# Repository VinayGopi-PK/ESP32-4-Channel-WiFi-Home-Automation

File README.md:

# ESP32 4-Channel Wi-Fi Home Automation

An **ESP32-based 4-channel Wi-Fi Home Automation Controller** designed for wireless control of electrical loads using four relay outputs.

The project includes a custom hardware design developed in **KiCad**, covering the schematic, PCB layout, power supply section, ESP32 programming interface, relay control circuitry, indicators, and PCB 3D visualization.

---

## Project Overview

This project is a compact **4-channel Wi-Fi Home Automation Controller** based on an ESP32 module.

The controller is designed to provide four independent relay-controlled outputs that can be operated through the ESP32's Wi-Fi connectivity.

The PCB integrates the ESP32 controller, isolated AC-to-DC power supply, 3.3 V regulation, USB programming interface, relay control circuitry, status indicators, and four relay outputs into a single custom PCB.

### Basic System Architecture

```text
                    AC INPUT
                       │
                       ▼
              ┌─────────────────┐
              │  Isolated AC-DC │
              │   Power Supply  │
              └────────┬────────┘
                       │
                       ▼
                  +5V DC Rail
                       │
             ┌─────────┴─────────┐
             │                   │
             ▼                   ▼
       3.3V Regulator       Relay Section
             │                   │
             ▼                   ▼
          ESP32 MCU        4 × Relays
             │                   │
             └─────────┬─────────┘
                       │
                 Wi-Fi Control
                       │
                       ▼
                 Home Appliances
```

---

## Main Features

* ESP32-based Wi-Fi controller
* 4 independent relay channels
* Custom PCB designed using KiCad
* Isolated AC-to-DC power supply section
* 5 V system power rail
* 3.3 V regulated supply for ESP32
* USB interface for programming and communication
* CP2102 USB-to-UART interface
* Auto-programming support
* BOOT and RESET controls
* Individual relay control circuitry
* Status indication LEDs
* Custom PCB layout
* Front and back copper routing
* 3D PCB visualization
* Manufacturing-oriented PCB design

---

## Hardware

| Component         | Function                                    |
| ----------------- | ------------------------------------------- |
| ESP32             | Main microcontroller and Wi-Fi connectivity |
| HLK-PM01          | Isolated AC-to-DC power supply              |
| AMS1117-3.3       | 3.3 V voltage regulation                    |
| CP2102            | USB-to-UART programming interface           |
| SANYOU SRD Relays | Switching of four output channels           |
| SS14              | Power protection / rectification section    |
| BOOT Button       | ESP32 boot-mode control                     |
| RESET Button      | ESP32 reset control                         |
| Status LEDs       | Power / system / channel indication         |
| Micro USB         | Power/programming interface                 |

---

## 4-Channel Relay Control

The PCB provides **four independent relay channels** for controlling external electrical loads.

```text
                    ESP32
                      │
          ┌───────────┼───────────┐───────────┐   
          │           │           │           │
          ▼           ▼           ▼           ▼
       Channel 1   Channel 2   Channel 3   Channel 4
          │           │           │           │
          ▼           ▼           ▼           ▼
       Relay 1     Relay 2     Relay 3     Relay 4
          │           │           │           │
          ▼           ▼           ▼           ▼
       LOAD 1      LOAD 2      LOAD 3      LOAD 4
```

Each relay channel is controlled independently by the ESP32.

---

## Power Supply

The PCB incorporates an **isolated AC-to-DC power supply section** to provide the required DC power for the controller.

The power architecture includes:

* AC input
* Isolated AC-to-DC conversion
* +5 V system rail
* 3.3 V regulation
* ESP32 power supply
* Relay power supply
* Power protection components

The design separates the low-voltage control circuitry from the incoming AC section through the isolated power supply.

---

## USB Programming Interface

The PCB includes a **CP2102 USB-to-UART interface** for programming and serial communication with the ESP32.

The programming section includes:

* Micro USB connector
* CP2102 USB-to-UART bridge
* ESP32 UART connection
* Auto-programming circuitry
* BOOT control
* RESET control

This allows the ESP32 firmware to be programmed without requiring a separate external USB-to-UART module.

---

## Indicators and Controls

The design includes dedicated user-interface components for operating and monitoring the controller.

### Controls

* BOOT button
* RESET button

### Indicators

* Power/system status indication
* Relay/channel status indication

The PCB uses compact SMD LEDs for status indication while retaining convenient physical controls for programming and reset operations.

---

## PCB Design

The complete PCB was designed using **KiCad**.

The design includes:

* Complete electrical schematic
* Component selection and footprint assignment
* PCB component placement
* Signal routing
* Power routing
* Ground plane
* Relay section
* AC input section
* USB programming section
* ESP32 section
* Front and back PCB layout
* 3D PCB visualization
* Manufacturing files

---

## PCB Design Preview

### Schematic

### PCB Front Layout

### PCB Back Layout

### 3D View

---

## Design Considerations

The PCB design considers the separation between the **AC mains section and low-voltage electronics**.

Important design considerations include:

* Isolation between AC input and low-voltage circuitry
* Dedicated power distribution
* Ground-plane implementation
* Appropriate PCB clearances
* Relay switching section
* ESP32 signal routing
* USB programming interface
* Component placement
* Manufacturing requirements

> **Safety note:** This project involves mains-voltage circuitry. The PCB should only be assembled, tested, and operated by appropriately qualified personnel using suitable electrical safety practices and enclosure/isolation measures.

---

## Design Tools

* **KiCad** — Schematic and PCB design
* **ESP32** — Embedded Wi-Fi controller
* **CP2102** — USB-to-UART interface

---

## Technical Highlights

**Microcontroller:** ESP32
**Wireless Communication:** Wi-Fi
**Relay Channels:** 4
**AC-DC Power Supply:** HLK-PM01
**Logic Supply:** 3.3 V
**USB-UART:** CP2102
**Relay:** SANYOU SRD Series
**PCB Design Tool:** KiCad
**PCB Type:** Custom PCB

---

## Repository Contents

The repository contains the project design files, PCB manufacturing files, documentation, and project images.

### KiCad Project

Contains:

* KiCad schematic
* KiCad PCB layout
* KiCad project files
* Component and footprint configuration files

### Documentation

Contains project-related documentation and component information.

### Gerber Files

Contains the generated PCB manufacturing files.

### Images

Contains:

* Schematic
* PCB front layout
* PCB back layout
* PCB 3D view

---

## Project Objective

The objective of this project was to design a **compact 4-channel ESP32-based Wi-Fi Home Automation Controller** integrating wireless control, relay switching, isolated power conversion, USB programming, and custom PCB design into a single hardware platform.

The project demonstrates skills in:

* Embedded system hardware design
* ESP32-based systems
* Wi-Fi-enabled control systems
* Power supply design
* Relay control
* USB-to-UART programming
* Schematic design
* PCB layout
* Component selection
* PCB manufacturing file generation

---

## Project Type

**ESP32 Embedded System | Wi-Fi Home Automation | Relay Controller | PCB Design**

**Design Software:** KiCad
**Controller:** ESP32

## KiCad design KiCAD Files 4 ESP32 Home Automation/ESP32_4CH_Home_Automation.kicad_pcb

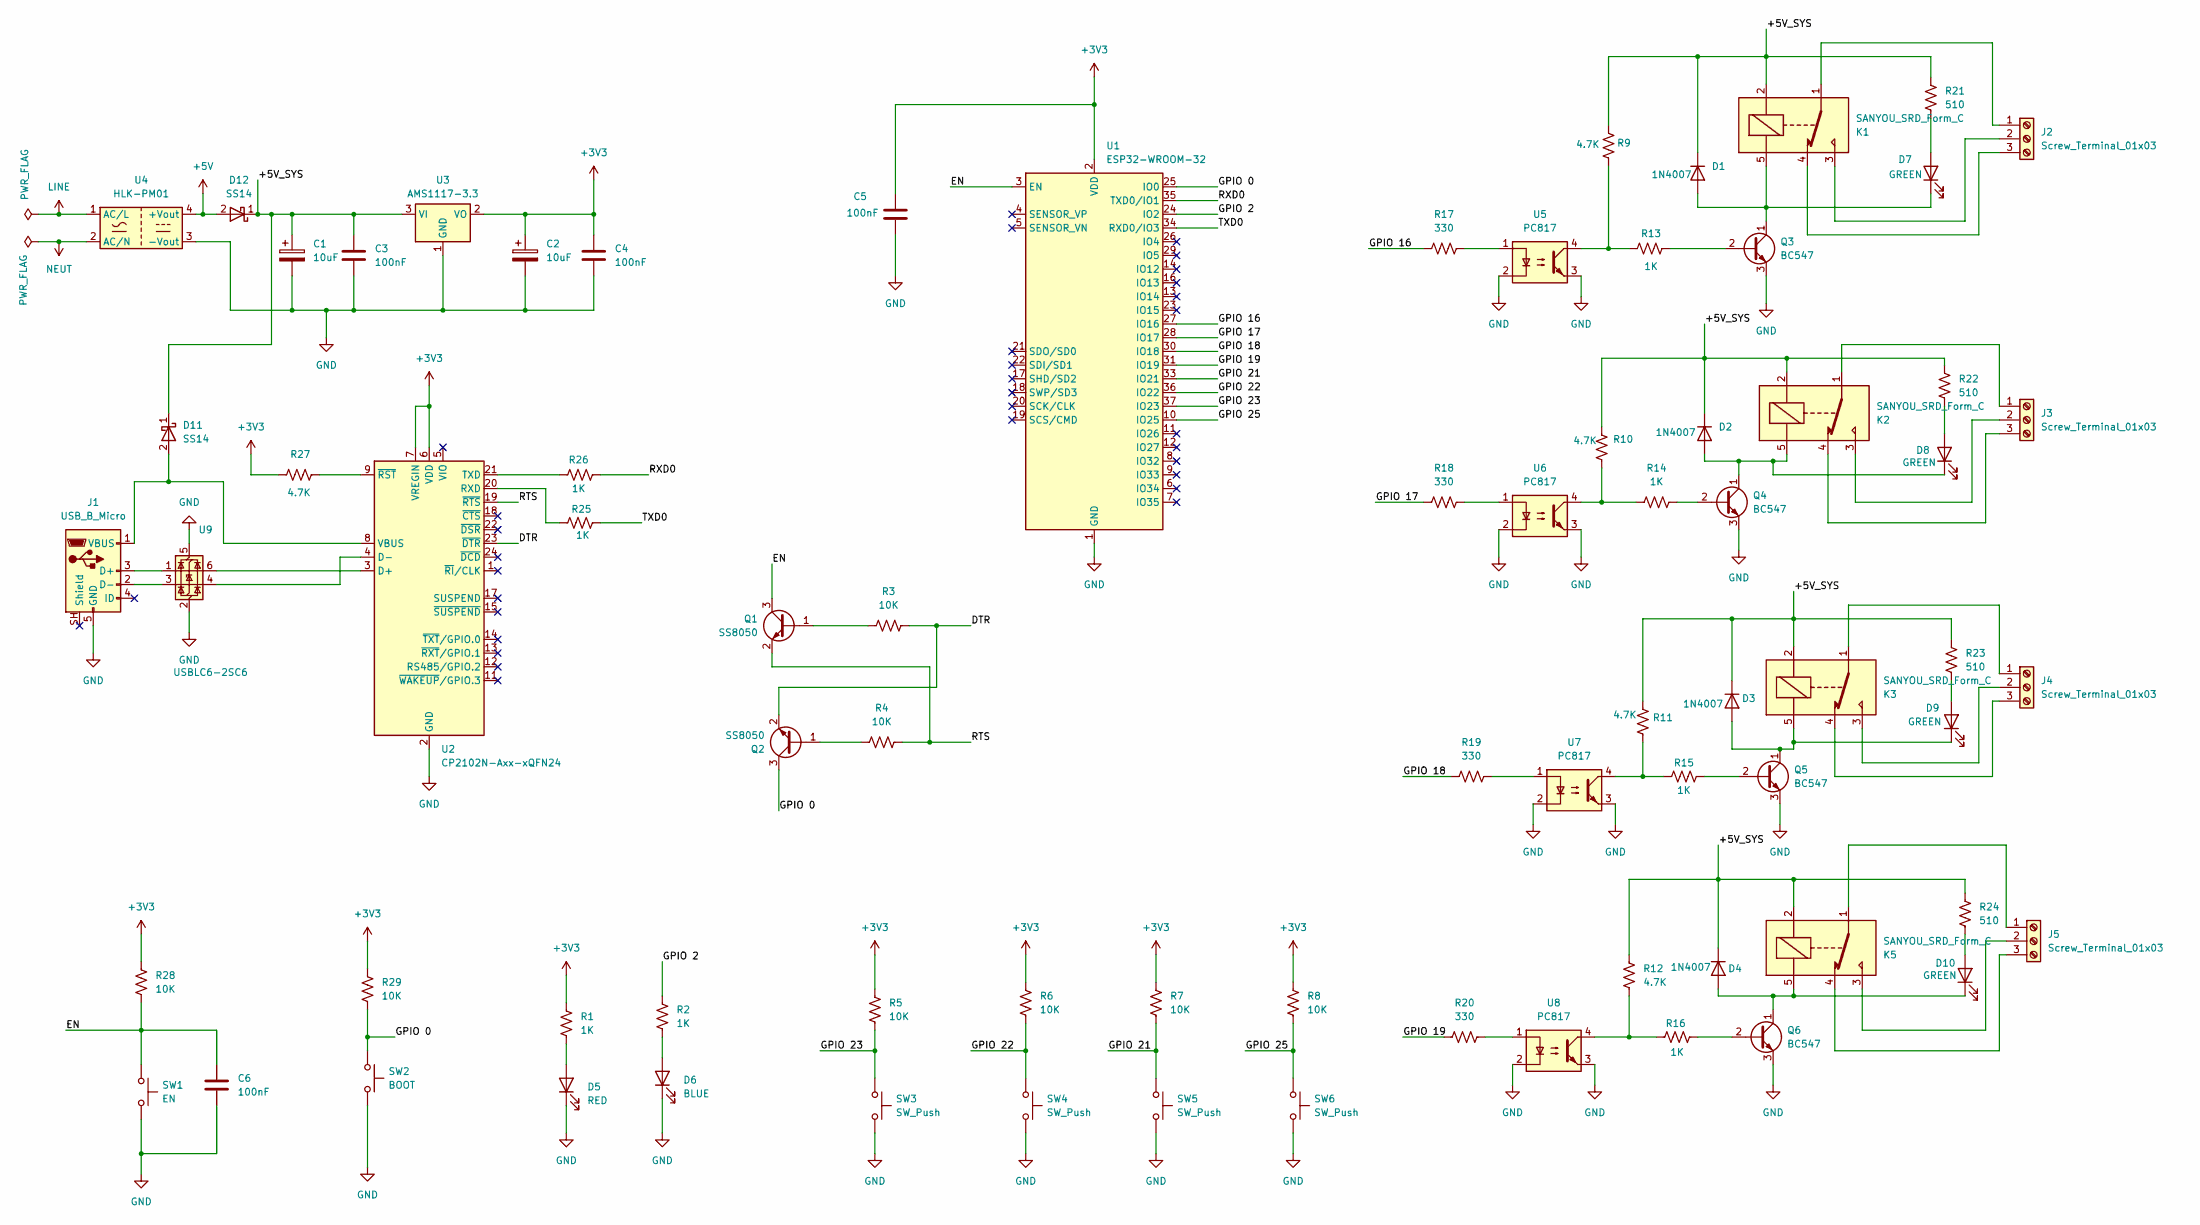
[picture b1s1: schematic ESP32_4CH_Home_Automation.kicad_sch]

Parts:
C1, C2: 10uF; C_1206_3216Metric
C3, C4, C5, C6: 100nF; C_0805_2012Metric
D1, D2, D3, D4: 1N4007; D_DO-41_SOD81_P10.16mm_Horizontal
D5: RED; LED_1206_3216Metric
D6: BLUE; LED_1206_3216Metric
D7, D8, D9, D10: GREEN; LED_1206_3216Metric
D11, D12: SS14; D_SMA
J1: USB_B_Micro; USB_Micro-B_Molex-105017-0001
J2, J3, J4, J5: Screw_Terminal_01x03; TerminalBlock_Phoenix_MKDS-1,5-3-5.08_1x03_P5.08mm_Horizont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
K1, K2, K3, K5: SANYOU_SRD_Form_C; Relay_SPDT_SANYOU_SRD_Series_Form_C
Q1, Q2: SS8050; SOT-23
Q3, Q4, Q5, Q6: BC547; TO-92_Inline
R1, R2, R25, R26: 1K; R_0805_2012Metric
R3, R4, R5, R6, R7, R8, R28, R29: 10K; R_0805_2012Metric
R9, R10, R11, R12: 4.7K; R_Axial_DIN0207_L6.3mm_D2.5mm_P7.62mm_Horizontal
R13, R14, R15, R16: 1K; R_Axial_DIN0207_L6.3mm_D2.5mm_P7.62mm_Horizontal
R17, R18, R19, R20: 330; R_Axial_DIN0207_L6.3mm_D2.5mm_P7.62mm_Horizontal
R21, R22, R23, R24: 510; R_Axial_DIN0207_L6.3mm_D2.5mm_P7.62mm_Horizontal
R27: 4.7K; R_0805_2012Metric
SW1: EN; SW_SPST_TL3342
SW2: BOOT; SW_SPST_TL3342
SW3, SW4, SW5, SW6: SW_Push; SW_PUSH_6mm
U1: ESP32-WROOM-32
U2: CP2102N-Axx-xQFN24; QFN-24-1EP_4x4mm_P0.5mm_EP2.6x2.6mm
U3: AMS1117-3.3; SOT-223-3_TabPin2
U4: HLK-PM01; Converter_ACDC_Hi-Link_HLK-PMxx
U5, U6, U7, U8: PC817; DIP-4_W7.62mm
U9: USBLC6-2SC6; SOT-23-6

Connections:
+3V3: C2.1, C4.1, C5.1, R1.1, R5.1, R6.1, R7.1, R8.1, R27.1, R28.2, R29.1, U1.2 (VDD), U2.6 (VDD), U2.7 (VREGIN), U3.2 (VO)
+5V: D12.2 (A), U4.4 (+Vout)
/+5V_SYS: C1.1, C3.1, D1.1 (K), D2.1 (K), D3.1 (K), D4.1 (K), D11.1 (K), D12.1 (K), K1.2, K2.2, K3.2, K5.2, R9.1, R10.1, R11.1, R12.1, R21.1, R22.1, R23.1, R24.1, U3.3 (VI)
/DTR: Q2.2 (E), R3.2, U2.23 (~DTR)
/EN: C6.1, Q1.3 (C), R28.1, SW1.1, U1.3 (EN)
/GPIO 0: Q2.3 (C), R29.2, SW2.1, U1.25 (IO0)
/GPIO 2: R2.1, U1.24 (IO2)
/GPIO 16: R17.1, U1.27 (IO16)
/GPIO 17: R18.1, U1.28 (IO17)
/GPIO 18: R19.1, U1.30 (IO18)
/GPIO 19: R20.1, U1.31 (IO19)
/GPIO 21: R7.2, SW5.1, U1.33 (IO21)
/GPIO 22: R6.2, SW4.1, U1.36 (IO22)
/GPIO 23: R5.2, SW3.1, U1.37 (IO23)
/GPIO 25: R8.2, SW6.1, U1.10 (IO25)
/RTS: Q1.2 (E), R4.2, U2.19 (~RTS)
/RXD0: R26.2, U1.35 (TXD0/IO1)
/TXD0: R25.2, U1.34 (RXD0/IO3)
GND: C1.2, C2.2, C3.2, C4.2, C5.2, C6.2, D5.1 (K), D6.1 (K), J1.5 (GND), Q3.3 (E), Q4.3 (E), Q5.3 (E), Q6.3 (E), SW1.2, SW2.2, SW3.2, SW4.2, SW5.2, SW6.2, U1.1 (GND), U1.15 (GND), U1.38 (GND), U1.39 (GND), U2.2 (GND), U2.25 (GND), U3.1 (GND), U4.3 (-Vout), U5.2, U5.3, U6.2, U6.3, U7.2, U7.3, U8.2, U8.3, U9.2 (GND), U9.5 (VBUS)
LINE: U4.1 (AC/L)
NEUT: U4.2 (AC/N)
unnamed: D1.2 (A), D7.1 (K), K1.5, Q3.1 (C)
unnamed: D2.2 (A), D8.1 (K), K2.5, Q4.1 (C)
unnamed: D3.2 (A), D9.1 (K), K3.5, Q5.1 (C)
unnamed: D5.2 (A), R1.2
unnamed: D6.2 (A), R2.2
unnamed: D7.2 (A), R21.2
unnamed: D8.2 (A), R22.2
unnamed: D9.2 (A), R23.2
unnamed: D10.2 (A), R24.2
unnamed: D4.2 (A), D10.1 (K), K5.5, Q6.1 (C)
unnamed: D11.2 (A), J1.1 (VBUS), U2.8 (VBUS)
unnamed: J1.3 (D+), U9.1 (I/O1)
unnamed: J1.2 (D-), U9.3 (I/O2)
unnamed: J2.1, K1.1
unnamed: J2.2, K1.3
unnamed: J2.3, K1.4
unnamed: J3.1, K2.1
unnamed: J3.2, K2.3
unnamed: J3.3, K2.4
unnamed: J4.1, K3.1
unnamed: J4.2, K3.3
unnamed: J4.3, K3.4
unnamed: J5.1, K5.1
unnamed: J5.2, K5.3
unnamed: J5.3, K5.4
unnamed: Q1.1 (B), R3.1
unnamed: Q2.1 (B), R4.1
unnamed: Q3.2 (B), R13.2
unnamed: Q4.2 (B), R14.2
unnamed: Q5.2 (B), R15.2
unnamed: Q6.2 (B), R16.2
unnamed: R10.2, R14.1, U6.4
unnamed: R11.2, R15.1, U7.4
unnamed: R12.2, R16.1, U8.4
unnamed: R9.2, R13.1, U5.4
unnamed: R17.2, U5.1
unnamed: R18.2, U6.1
unnamed: R19.2, U7.1
unnamed: R20.2, U8.1
unnamed: U2.3 (D+), U9.6 (I/O1)
unnamed: U2.4 (D-), U9.4 (I/O2)
unnamed: R25.1, U2.20 (RXD)
unnamed: R26.1, U2.21 (TXD)
unnamed: R27.2, U2.9 (~RST)

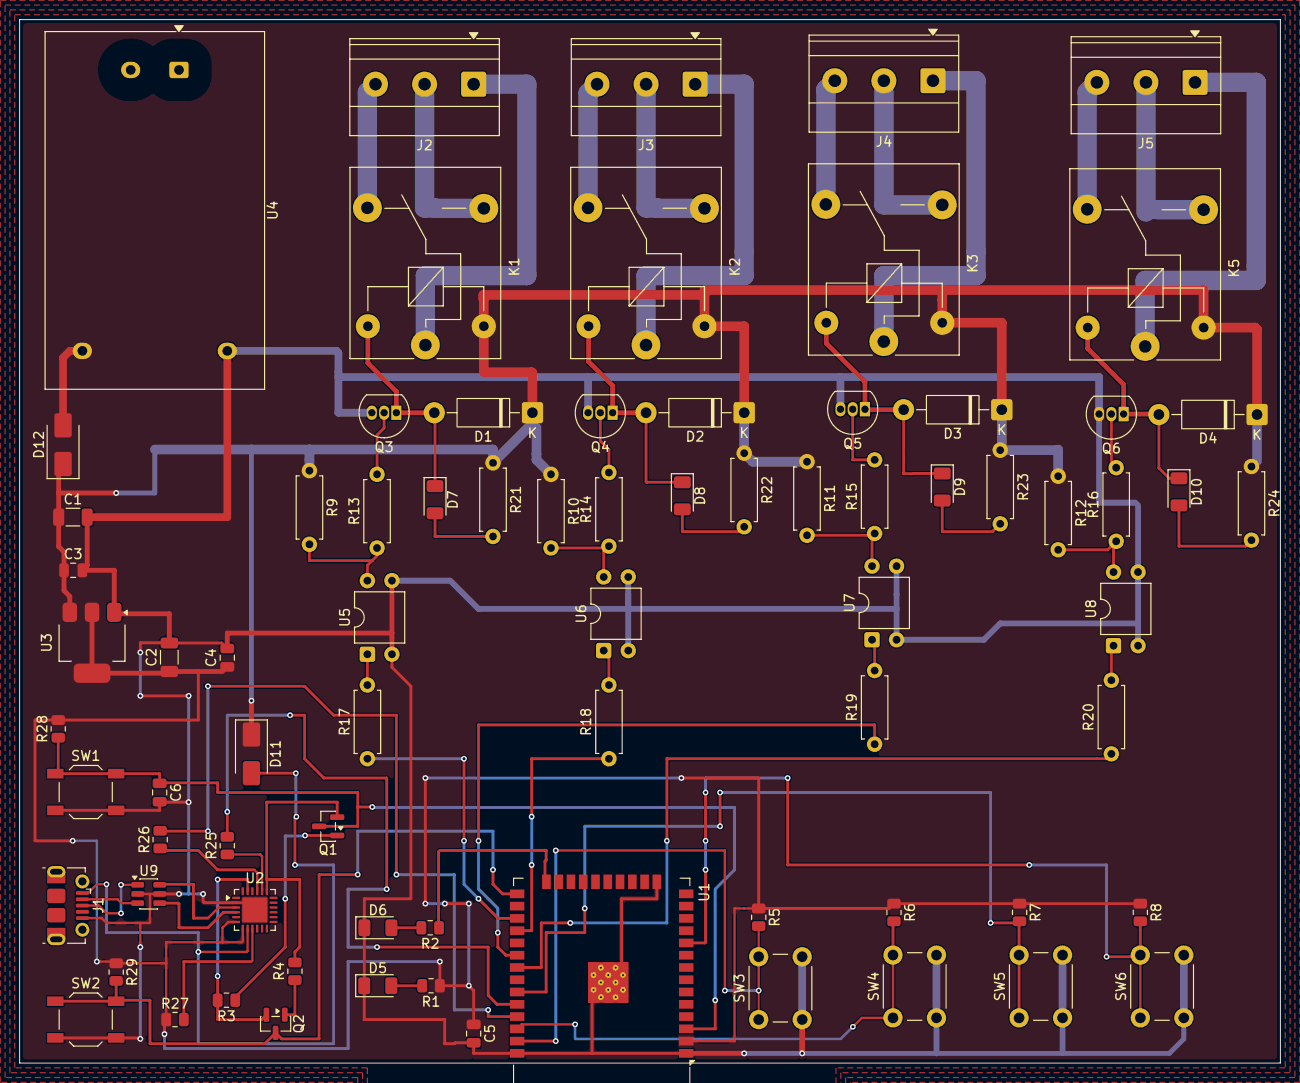
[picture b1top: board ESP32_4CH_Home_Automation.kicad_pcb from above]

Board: 2 copper layers, 130.5 x 108.0 mm, 77 parts (0 on the bottom side), 63 nets.
